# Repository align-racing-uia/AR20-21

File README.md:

<h1 align="center"> Align Racing 2021 </h1> <br>
<p align="center">
    
</p>

<!-- START doctoc generate TOC please keep comment here to allow auto update -->
<!-- DON'T EDIT THIS SECTION, INSTEAD RE-RUN doctoc TO UPDATE -->
## Table of contents

- [Introduction](#introduction)
- [Align Racing UiA](#alignracinguia)
- [Rules for file structure](#rulesforfilestructure)
- [License](#license)

<!-- END doctoc generated TOC please keep comment here to allow auto update -->

## Introduction

This is the repository for Align Racing's formula student race car's different systems.

## Align Racing UiA

<a href="http://www.alignracing.no/">Align Racing UiA (AR)</a> is a multidisciplinary student organisation at <a href="https://www.uia.no/">The University of Agder (UiA)</a>, that take part in the world’s largest yearly engineering competition; <a href="https://www.imeche.org/events/formula-student">Formula Student (FS)</a>. The organisation continuously consists of around 60 students, from a wide variety of disciplines. The competition includes developing, building, budgeting and marketing a small scale formula type racing car. AR takes this a bit further by having more focus on developing a strong organisation, open for all disciplines, that gives the members a taste of future work-life.

## Rules for directory structure
<h4>General directory structure:</h4>

* AR”YEAR”
    * AR”YEAR”_“PROJECT”
        - AR”YEAR”_“SUBPROJECT”
            - “PROJECT”_code
            - “PROJECT”_datasheets
            - “PROJECT”_images
            - “PROJECT”_schematic
            - “PROJECT”_simulink

<h4>Directory structure example:</h4>

* AR19
    * AR19_ETC
        - AR19_ETC_ACM_ETB
            - ACM_ETB_code
            - ACM_ETB_datasheets
            - ACM_ETB_images
            - ACM_ETB_schematic
            - ACM_ETB_simulink

## License
All content included in this Git repository is under the license:

Creative Commons Attribution-NonCommercial-ShareAlike 4.0 International

You are free to:
* <b> Share </b> — copy and redistribute the material in any medium or format
* <b> Adapt </b> — remix, transform, and build upon the material

Under the following terms:
* <b> Attribution </b> — You must give appropriate credit, provide a link to the license, and indicate if changes were made. You may do so in any reasonable manner, but not in any way that suggests the licensor endorses you or your use.
* <b> NonCommercial </b> — You may not use the material for commercial purposes.
* <b> ShareAlike </b> — If you remix, transform, or build upon the material, you must distribute your contributions under the same license as the original.
* <b> No additional restrictions </b> — You may not apply legal terms or technological measures that legally restrict others from doing anything the license permits.

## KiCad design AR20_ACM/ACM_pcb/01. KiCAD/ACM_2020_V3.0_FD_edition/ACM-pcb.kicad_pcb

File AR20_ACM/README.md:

## ACM 2020

### Changelog:

**27.07.2019:**
- Added: Protection circuit
- Added: Atmega Clock pass-through
- Moved: External oscillator from MCP to Atmega.

**28.07.2019:**
- Changed:	Orientation of tag connector in schematics
- Added:	Connector with I/O
- Added:	Overcurrent protection with polyfuse
- Added:	Overvoltage protection with zener diode
- Added:	Reverse polarity protection with diode
- Generated:Bill of Materials
- Added:	JAE IL-WX Series 0.8mm Pitch 30 Way connector
- Added:	RGB LED
- Added: P-mosfet for reverse polarity-protection
- Positioned power management (OC, OV, RP) in a 12x4mm space.
- Started tracing

**29.07.2019:**
- Moved: Protection circuit
- Changed board layout
- Changed viasize from 0.2 to 0.3
- Routing of tracks

**30.07.2019:**
- Added 3D components
- Removed all Tracks
- Added DC/DC converter
- Changed footprint of connector
- Added LP-filter to Atmega Avcc (Datasheet page 348)

**03.08.2019:**
- Changed folder structure
- Added mounting hole in schematics
- Removed LDO
- Added 5V switching regulator
- Changed Connector footprint
- Added track and via info from JLCPCB (2-Layers)

**04.08.2019:**
- Completed BOM on Google Drive
- Added 2x 10uF input Capacitor for regulator
- Moved documentation to main

**06.10.2019:**
- Moved resistors and capacitors away from microcontrollers
- Changed from Atmega328PB to Atmega328P (NB! Need to check circuit PWM and such)
- Disconnected all output pins on the Atmega328P
- Created a ACM simulation folder
- Connected pins that are equal to Atmega328PB

**26.09.2020:**
- Changed reverse polarity protection
- Added 5v USB backwards current protection

**27.09.2020** 
- Changed RGB led from from common Anode to common Cathode

**30.09.2020 - V3.0**
- Started upgrading to CAN FD chips. 

### ACM 2019 - Documentation

List of possible imporvements for ACM 2019
  + Remove the Fuse as it is 20\% of the total cost. Change it to a soldered SMD fuse or a diode.
   % Soruce https://docs.google.com/spreadsheets/d/1aR7CLCnCkN-1Qp3qICuXivDnihjTyPiA6Gjus2cEa0c/edit#gid=311613741&range=R12:R13
  
  + More I/O (Especially 2 interrupt) or change board dimension ratio. (1:1) like a flight controller
  
  + Remove castellated holes, since it makes the boards less reliable, and are also harder to manufacture.  
  
  + Change the led to a larger led for easy board manufacturing.
  
  + Change I/O to only one side of the board for hot swap.
  
  + ICSP take a large amout of space, change it to pads or small programming connector.
  
  + Change the width of the PCB to X*2,54mm so that it fits standard pin layout
  
  + Remove clock capacitors as "CSTNE16M0V530000R0" got 15uF embedded. Doesn't not require external load capacitors
  
  + Add a diode with a capacitor after. ACM reset due to low voltage when high current draw.
  
  + Possibility for UART out
  
  + Add low pass filter for the A/D converter (AVcc input) (See page 14 in 328p datasheet)

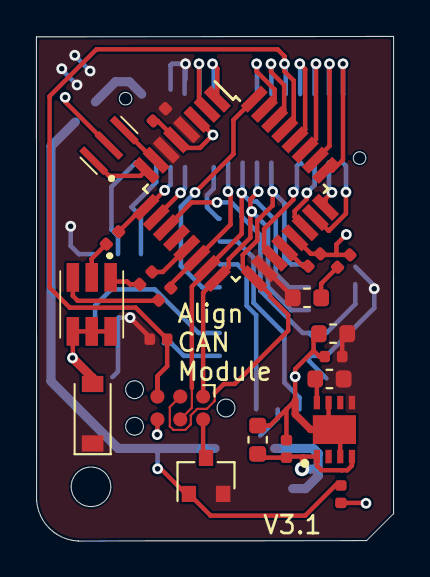
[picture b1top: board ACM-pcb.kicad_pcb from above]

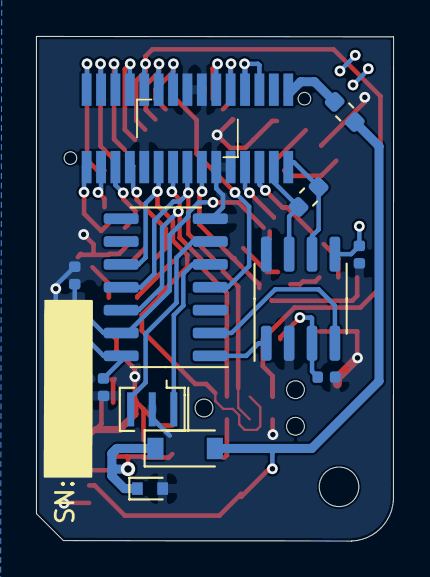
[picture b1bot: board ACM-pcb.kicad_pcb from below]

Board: 2 copper layers, 19.8 x 28.0 mm, 34 parts (13 on the bottom side), 42 nets.

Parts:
C1, C2, C3, C4, C5, C6, C7, C8: 0.1uF; C_0402_1005Metric
C10, C11: 10uF; C_0603_1608Metric
D1: 15V; D_SOD-523
D2: D_Zener_KDZVTR5.6B; D_Zener_KDZV5.6B_SOD-123
D4: D_Schottky_MBR0520LT1G; D_schotky_MBR0520LT1G
F1: 250mA; Fuse_0603_1608Metric
H1: M2 Mouting hole; MountingHole_2.2mm_M2
J1: TC2030-MCP-NL; Tag-Connect_TC2030-IDC-NL_2x03_P1.27mm_Vertical
L1: 10uH; L_0603_1608Metric
L2: 2.2 µH; L_0603_1608Metric
LED1: ASMB-TTF0-0A20B; ASMBTTF00A20B
P1: Conn_02x15_Odd_Even; IL-WX-30SB-VF-BE
Q1: Q_PMOS_DMP3099L-13; Pmos_DMP3099L-13
R1, R2, R6: 10K Ohm; R_0402_1005Metric
R3: 220Ω; R_0402_1005Metric
R4: 200Ω; R_0402_1005Metric
R5: 190Ω; R_0402_1005Metric
R7: 120Ω; R_0603_1608Metric
U1: ATmega328P-AU; TQFP-32_7x7mm_P0.8mm
U2: MCP2542FDxMF; SOIC_MCP2542FD
U3: NCV890430MW50TXG; SON65P300X300X100-9N
U4: MCP2517FD-xSL; Can_MCP2517FD_SOIC
Y1: 16.0Mhz; CSTNE16M0V530000R0
Y2: 20.0 Mhz; Resonator_CSTNE20M0V51Z000R0

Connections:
12V_fused: D4.2, F1.1, Q1.1, R2.2
+5V: C1.1, C5.1, C6.1, C7.1, C8.2, C11.1, D2.1, L1.1, L2.2, P1.24, P1.26, Q1.2, R1.1, R6.1, U1.4, U1.6, U1.18, U2.3, U2.5, U3.5, U4.14
+12V: F1.2, P1.30
+12V_Safe: C4.1, C10.1, D1.1, D4.1, U3.1, U3.4
/BLUE_LED: P1.17, R5.2, U1.14
/CAN_CS: R6.2, U1.11, U4.13
/CAN_INT: U1.32, U4.4
/GREEN_LED: P1.25, R4.2, U1.9
/MISO: J1.1, P1.13, U1.16, U4.12
/MOSI: J1.4, P1.15, U1.15, U4.11
/RED_LED: R3.2, U1.13
/RXCAN: U2.4, U4.2
/Reset: J1.5, P1.10, R1.2, U1.29
/SCK: J1.3, P1.11, U1.17, U4.10
/TXCAN: U2.1, U4.1
/U-Pin1: P1.1, U1.23
/U-Pin2: P1.2, U1.25
/U-Pin3: P1.3, U1.24
/U-Pin4: P1.4, U1.26
/U-Pin5: P1.5, U1.22
/U-Pin6: P1.6, U1.27
/U-Pin7: P1.7, U1.19
/U-Pin8: P1.8, U1.28
/U-Pin12: P1.12, U1.30
/U-Pin14: P1.14, U1.31
/U-Pin20: P1.20, U1.1
/U-Pin22: P1.22, U1.2
/U-Pin23: P1.23, U1.10
/U-Pin27: P1.27, R7.1, U2.7
/U-Pin29: P1.29, R7.2, U2.6
GND: C1.2, C2.2, C3.1, C4.2, C5.2, C6.2, C7.2, C8.1, C10.2, C11.2, D1.2, D2.2, J1.6, LED1.2, LED1.4, LED1.6, P1.9, P1.16, P1.18, P1.19, P1.21, R2.1, U1.3, U1.5, U1.21, U2.2, U2.8, U3.3, U3.7, U3.9, U4.7, Y1.2, Y2.2
unnamed: C2.1, U1.20
unnamed: C3.2, L1.2
unnamed: J1.2, Q1.3
unnamed: L2.1, U3.8
unnamed: LED1.1, R3.1
unnamed: LED1.3, R4.1
unnamed: LED1.5, R5.1
unnamed: U1.7, Y1.3
unnamed: U1.8, Y1.1
unnamed: U4.5, Y2.1
unnamed: U4.6, Y2.3

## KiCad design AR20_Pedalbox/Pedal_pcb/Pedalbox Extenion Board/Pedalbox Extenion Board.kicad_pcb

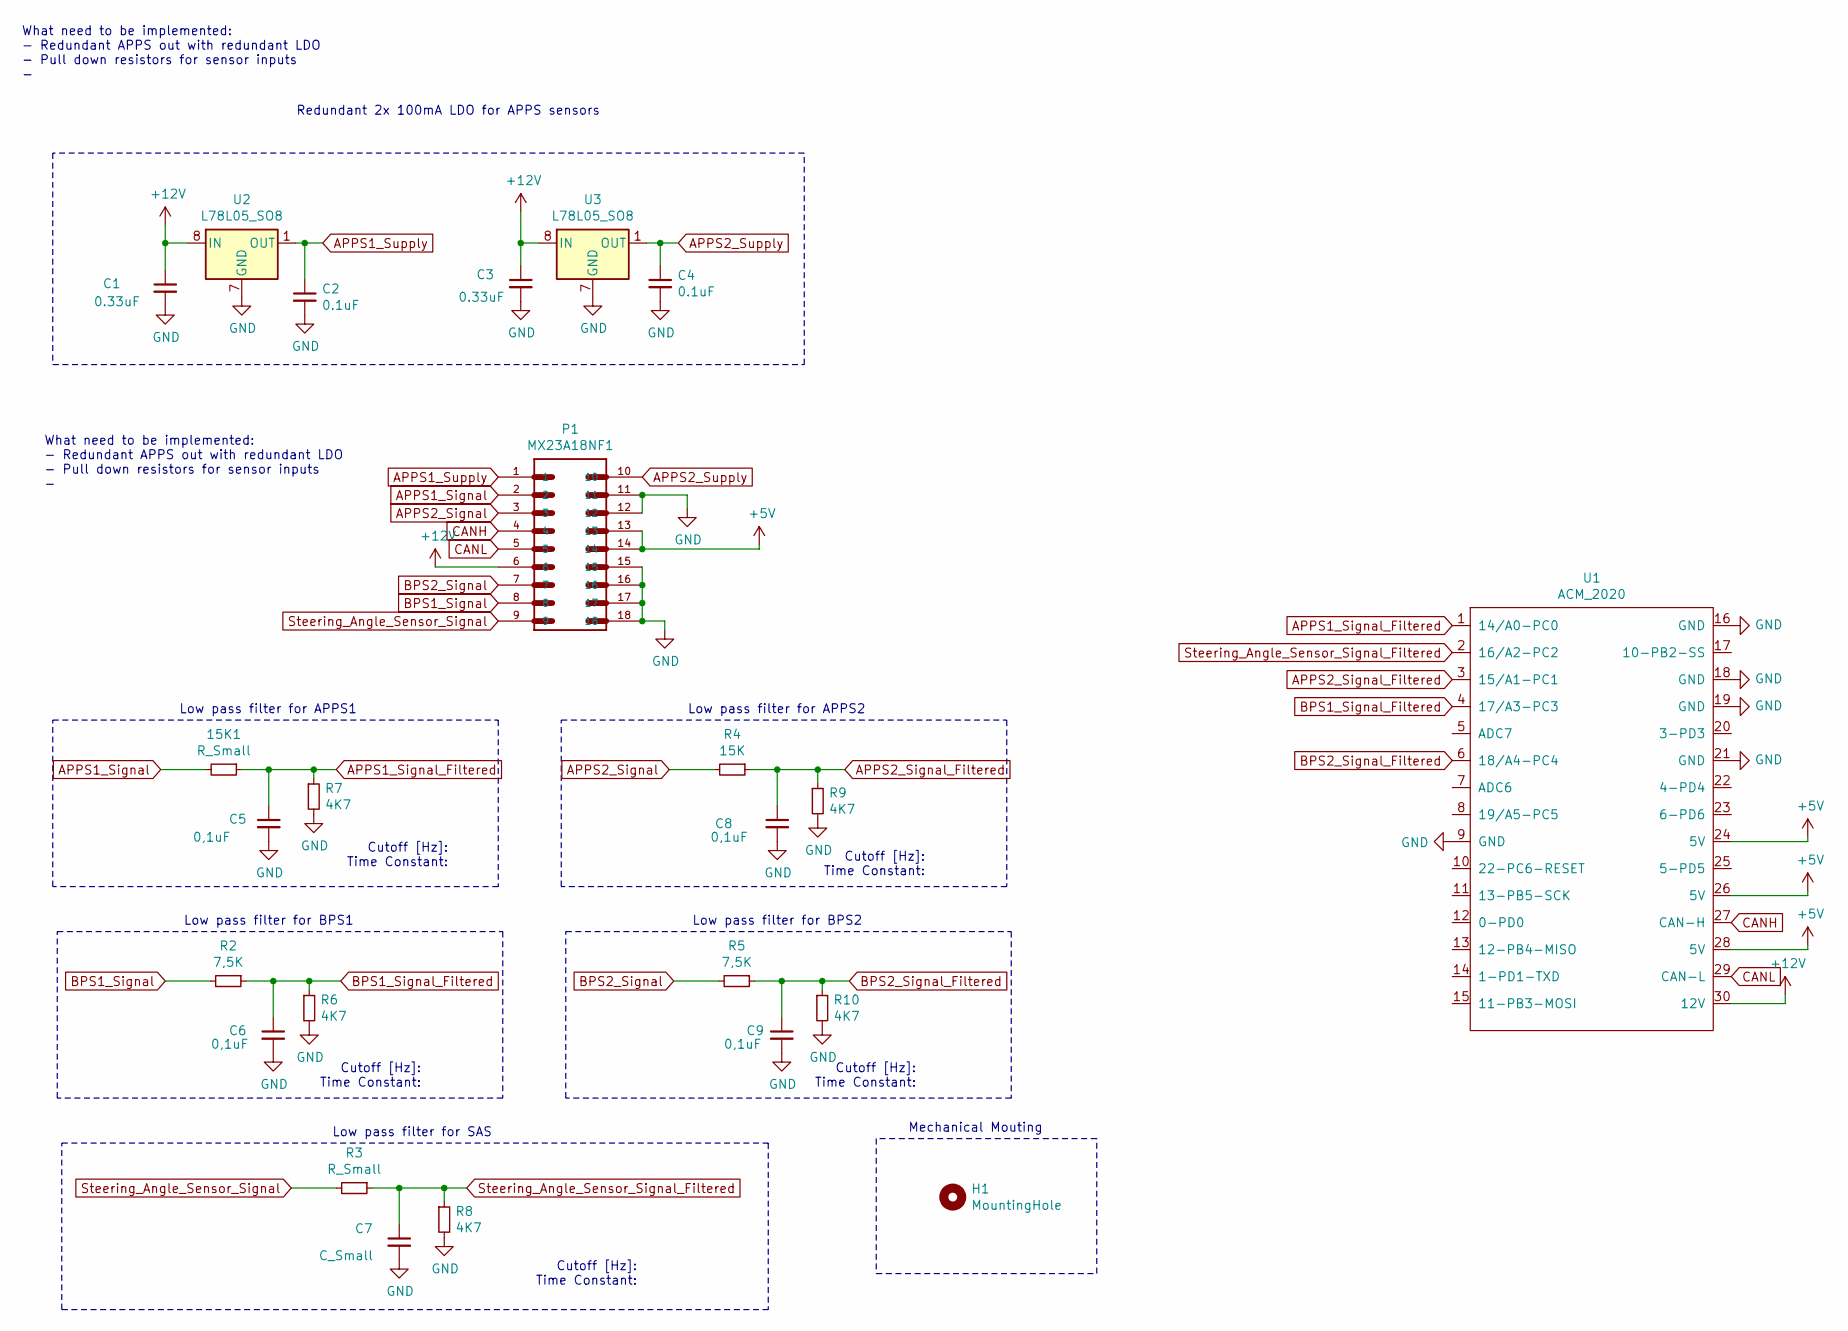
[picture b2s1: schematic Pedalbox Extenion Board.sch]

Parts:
15K1: R_Small; R_0603_1608Metric_Pad1.05x0.95mm_HandSolder
C1, C3: 0.33uF; C_0603_1608Metric_Pad1.05x0.95mm_HandSolder
C2, C4: 0.1uF; C_0603_1608Metric_Pad1.05x0.95mm_HandSolder
C5, C6, C8, C9: 0,1uF; C_0603_1608Metric_Pad1.05x0.95mm_HandSolder
C7: C_Small; C_0603_1608Metric_Pad1.05x0.95mm_HandSolder
H1: MountingHole; MountingHole_2.2mm_M2
P1: MX23A18NF1; JAE_MX23A18NF1
R2, R5: 7,5K; R_0603_1608Metric_Pad1.05x0.95mm_HandSolder
R3: R_Small; R_0603_1608Metric_Pad1.05x0.95mm_HandSolder
R4: 15K; R_0603_1608Metric_Pad1.05x0.95mm_HandSolder
R6, R7, R8, R9, R10: 4K7; R_0603_1608Metric_Pad1.05x0.95mm_HandSolder
U1: ACM_2020; ACM_2020_Footprint_wo_silk
U2, U3: L78L05_SO8; SOIC-8_3.9x4.9mm_P1.27mm

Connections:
+5V: P1.13, P1.14, U1.24 (5V), U1.26 (5V), U1.28 (5V)
+12V: C1.1, C3.1, P1.6, U1.30 (12V), U2.8 (IN), U3.8 (IN)
APPS1_Signal: 15K1.2, P1.2
APPS1_Signal_Filtered: 15K1.1, C5.1, R7.1, U1.1 (14/A0-PC0)
APPS1_Supply: C2.1, P1.1, U2.1 (OUT)
APPS2_Signal: P1.3, R4.2
APPS2_Signal_Filtered: C8.1, R4.1, R9.1, U1.3 (15/A1-PC1)
APPS2_Supply: C4.1, P1.10, U3.1 (OUT)
BPS1_Signal: P1.8, R2.2
BPS1_Signal_Filtered: C6.1, R2.1, R6.1, U1.4 (17/A3-PC3)
BPS2_Signal: P1.7, R5.2
BPS2_Signal_Filtered: C9.1, R5.1, R10.1, U1.6 (18/A4-PC4)
CANH: P1.4, U1.27 (CAN-H)
CANL: P1.5, U1.29 (CAN-L)
GND: C1.2, C2.2, C3.2, C4.2, C5.2, C6.2, C7.2, C8.2, C9.2, P1.11, P1.12, P1.15, P1.16, P1.17, P1.18, R6.2, R7.2, R8.2, R9.2, R10.2, U1.9 (GND), U1.16 (GND), U1.18 (GND), U1.19 (GND), U1.21 (GND), U2.2 (GND), U2.3 (GND), U2.6 (GND), U2.7 (GND), U3.2 (GND), U3.3 (GND), U3.6 (GND), U3.7 (GND)
Steering_Angle_Sensor_Signal: P1.9, R3.2
Steering_Angle_Sensor_Signal_Filtered: C7.1, R3.1, R8.1, U1.2 (16/A2-PC2)

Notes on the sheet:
Redundant 2x 100mA LDO for APPS sensors
What need to be implemented: - Redundant APPS out with redundant LDO - Pull down resistors for sensor inputs -
Low pass filter for APPS1
Low pass filter for APPS2
Cutoff [Hz]: Time Constant:
Low pass filter for BPS1
Low pass filter for BPS2
Low pass filter for SAS
Mechanical Mouting

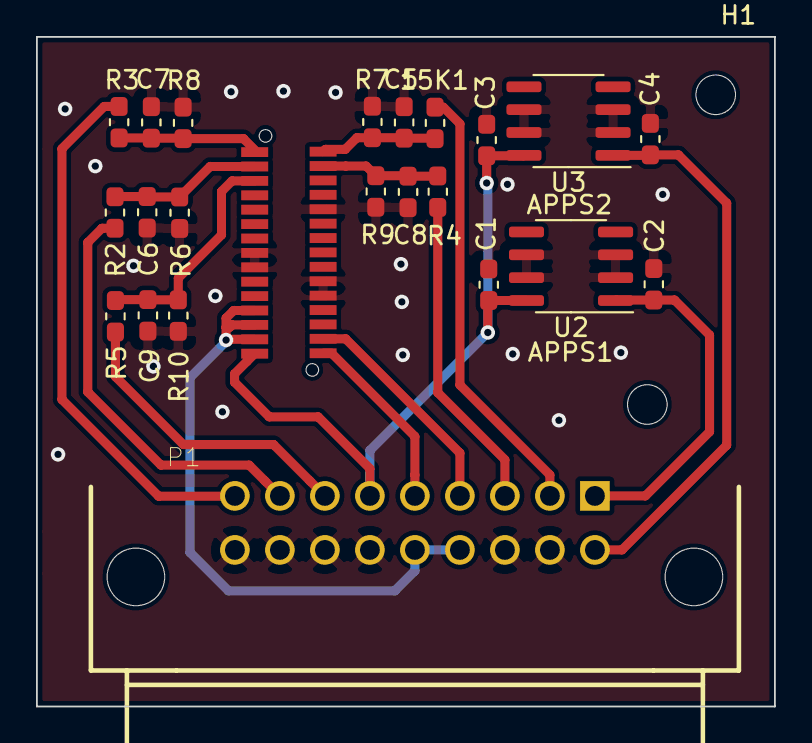
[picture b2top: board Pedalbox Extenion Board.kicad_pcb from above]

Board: 2 copper layers, 41.0 x 37.2 mm, 24 parts (0 on the bottom side), 17 nets.

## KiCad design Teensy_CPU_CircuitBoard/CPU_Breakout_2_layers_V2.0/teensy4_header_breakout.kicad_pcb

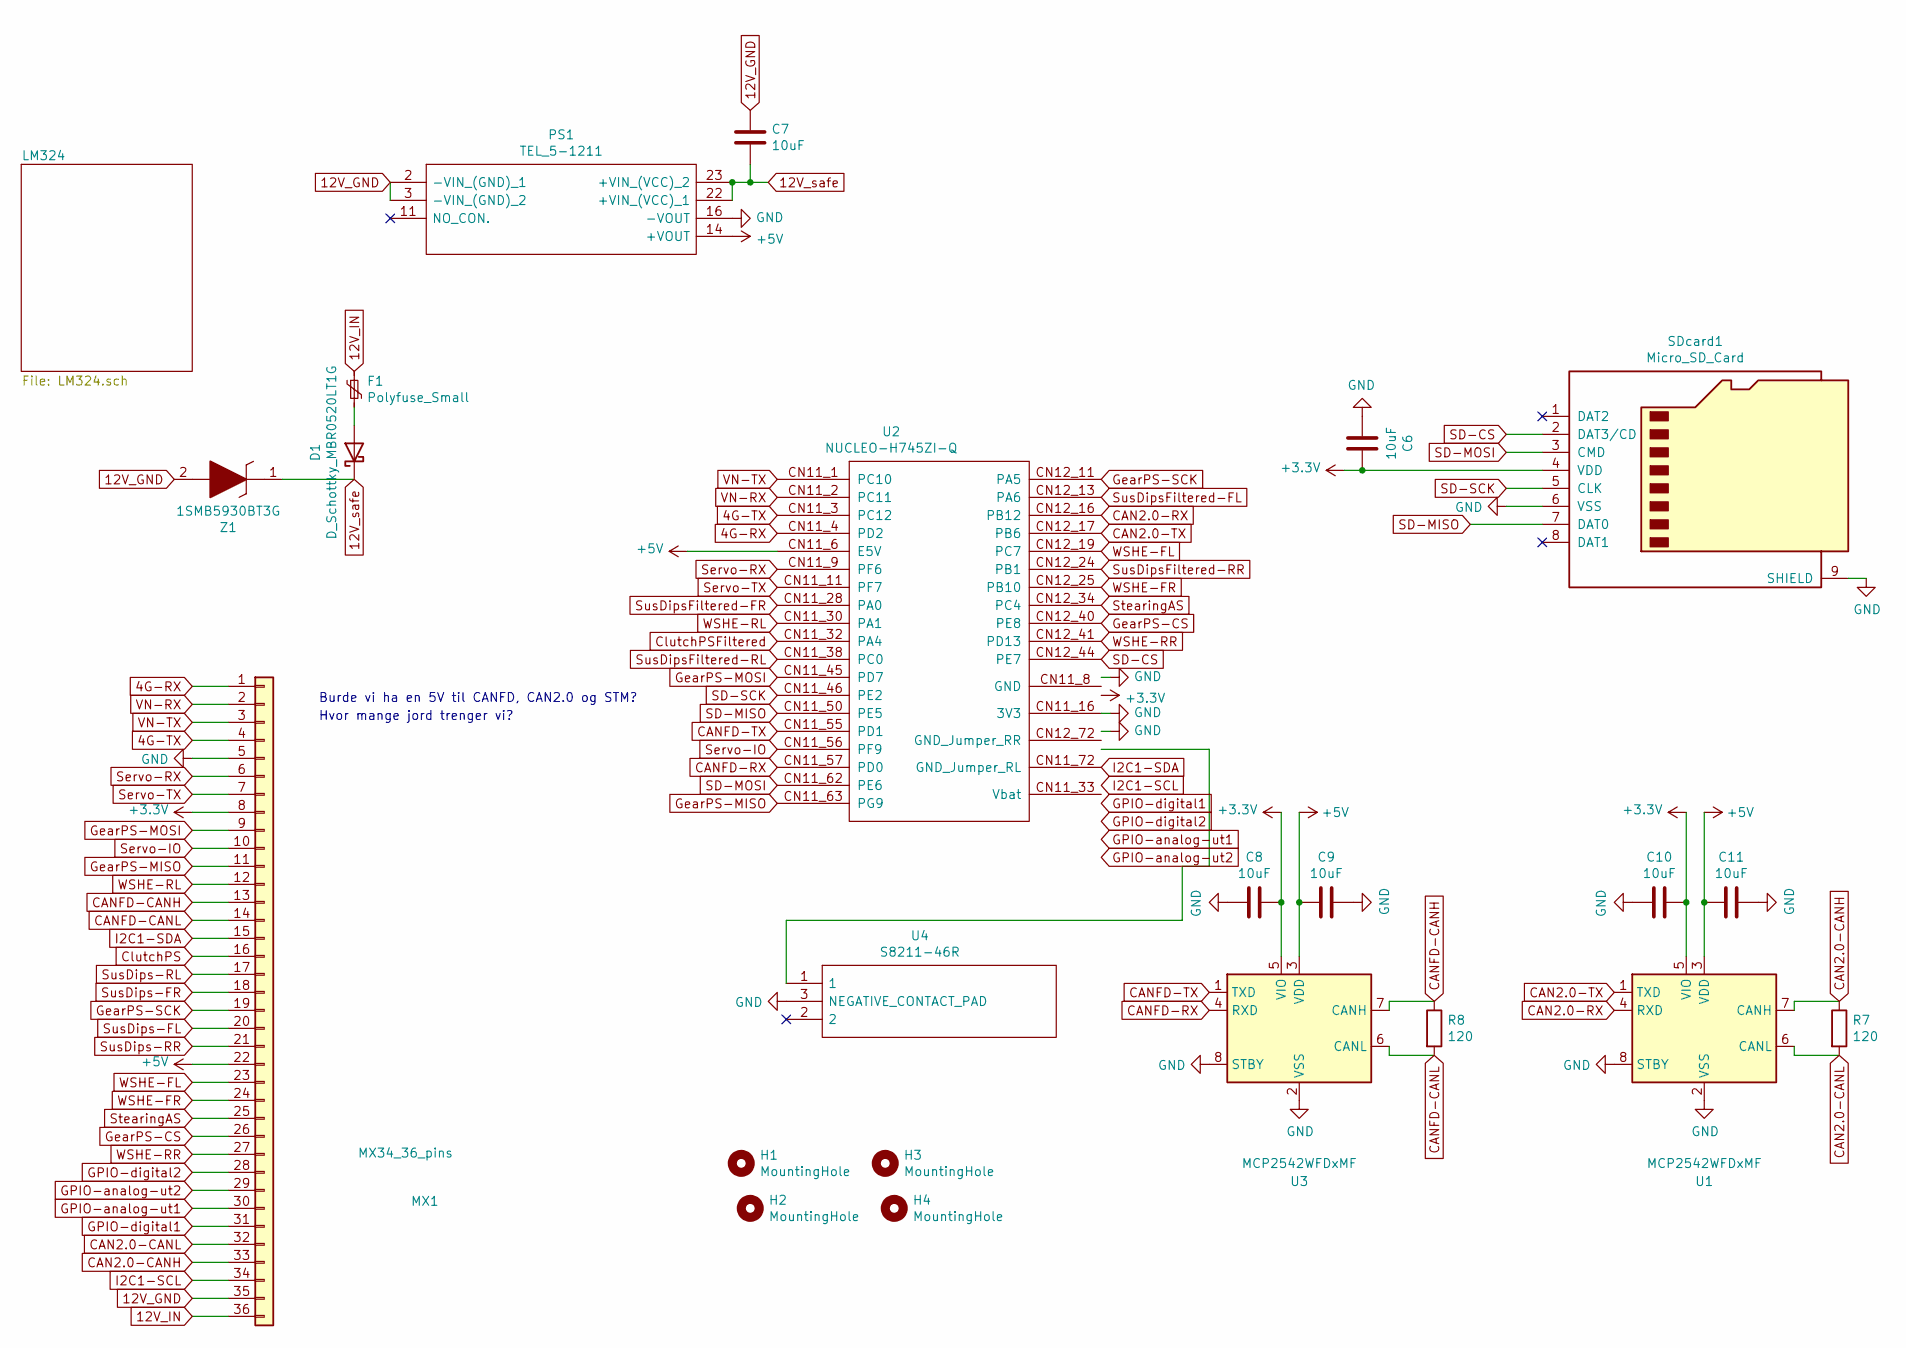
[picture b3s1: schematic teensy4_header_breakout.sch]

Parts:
C6, C7, C8, C9, C10, C11: 10uF; C_0603_1608Metric
D1: D_Schottky_MBR0520LT1G; D_SOD-123-MBR0520LT1G
F1: Polyfuse_Small; R_1210_3225Metric_Pad1.30x2.65mm_HandSolder
H1, H2, H3, H4: MountingHole; MountingHole_3.2mm_M3_ISO14580_Pad_TopBottom
MX1: MX34_36_pins; Connector_MX34_36pins
PS1: TEL_5-1211; TEL51211; Manufacturer_Part_Number TEL 5-1211; Mouser Part Number 495-TEL-5-1211
R7, R8: 120; R_0603_1608Metric_Pad0.98x0.95mm_HandSolder
SDcard1: Micro_SD_Card; Molex_502774-0891
U1, U3: MCP2542WFDxMF; DFN-8-1EP_3x3mm_P0.65mm_EP1.55x2.4mm
U2: NUCLEO-H745ZI-Q; MODULE_NUCLEO-F429ZI
U4: S8211-46R; Manufacturer_Part_Number S8211-46R; Mouser Part Number 855-S8211-46R
Z1: 1SMB5930BT3G; DIOM5436X247N; Manufacturer_Part_Number 1SMB5930BT3G; Mouser Part Number 863-1SMB5930BT3G

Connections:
4G-RX: MX1.1, U2.CN11_4 (PD2)
4G-TX: MX1.4, U2.CN11_3 (PC12)
12V_GND: C7.1, MX1.35, PS1.2 (-VIN_(GND)_1), PS1.3 (-VIN_(GND)_2), Z1.2
12V_IN: F1.1, MX1.36
12V_safe: C7.2, D1.1 (K), PS1.22 (+VIN_(VCC)_1), PS1.23 (+VIN_(VCC)_2), Z1.1
+5V: C9.1, C11.1, MX1.22, PS1.14 (+VOUT), U1.3 (VDD), U2.CN11_6 (E5V), U3.3 (VDD)
CAN2.0-CANH: MX1.33, R7.1, U1.7 (CANH)
CAN2.0-CANL: MX1.32, R7.2, U1.6 (CANL)
CAN2.0-RX: U1.4 (RXD), U2.CN12_16 (PB12)
CAN2.0-TX: U1.1 (TXD), U2.CN12_17 (PB6)
CANFD-CANH: MX1.13, R8.1, U3.7 (CANH)
CANFD-CANL: MX1.14, R8.2, U3.6 (CANL)
CANFD-RX: U2.CN11_57 (PD0), U3.4 (RXD)
CANFD-TX: U2.CN11_55 (PD1), U3.1 (TXD)
ClutchPS: MX1.16; also elsewhere on the board
ClutchPSFiltered: U2.CN11_32 (PA4); also elsewhere on the board
GPIO-analog-ut1: MX1.30, U2.CN12_50
GPIO-analog-ut2: MX1.29, U2.CN12_60
GPIO-digital1: MX1.31, U2.CN12_22
GPIO-digital2: MX1.28, U2.CN12_62
GearPS-CS: MX1.26, U2.CN12_40 (PE8)
GearPS-MISO: MX1.11, U2.CN11_63 (PG9)
GearPS-MOSI: MX1.9, U2.CN11_45 (PD7)
GearPS-SCK: MX1.19, U2.CN12_11 (PA5)
I2C1-SCL: MX1.34, U2.CN12_3
unnamed: D1.2 (A), F1.2
unnamed: U2.CN11_33 (Vbat), U4.1
SD-CS: SDcard1.2 (DAT3/CD), U2.CN12_44 (PE7)
SD-MISO: SDcard1.7 (DAT0), U2.CN11_50 (PE5)
SD-MOSI: SDcard1.3 (CMD), U2.CN11_62 (PE6)
SD-SCK: SDcard1.5 (CLK), U2.CN11_46 (PE2)
Servo-IO: MX1.10, U2.CN11_56 (PF9)
Servo-RX: MX1.6, U2.CN11_9 (PF6)
Servo-TX: MX1.7, U2.CN11_11 (PF7)
StearingAS: MX1.25, U2.CN12_34 (PC4)
SusDips-FL: MX1.20; also elsewhere on the board
SusDips-FR: MX1.18; also elsewhere on the board
SusDips-RL: MX1.17; also elsewhere on the board
SusDips-RR: MX1.21; also elsewhere on the board
SusDipsFiltered-FL: U2.CN12_13 (PA6); also elsewhere on the board
SusDipsFiltered-FR: U2.CN11_28 (PA0); also elsewhere on the board
SusDipsFiltered-RL: U2.CN11_38 (PC0); also elsewhere on the board
SusDipsFiltered-RR: U2.CN12_24 (PB1); also elsewhere on the board
VN-RX: MX1.2, U2.CN11_2 (PC11)
VN-TX: MX1.3, U2.CN11_1 (PC10)
WSHE-FL: MX1.23, U2.CN12_19 (PC7)
WSHE-FR: MX1.24, U2.CN12_25 (PB10)
WSHE-RL: MX1.12, U2.CN11_30 (PA1)
WSHE-RR: MX1.27, U2.CN12_41 (PD13)

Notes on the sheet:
Burde vi ha en 5V til CANFD, CAN2.0 og STM?
Hvor mange jord trenger vi?

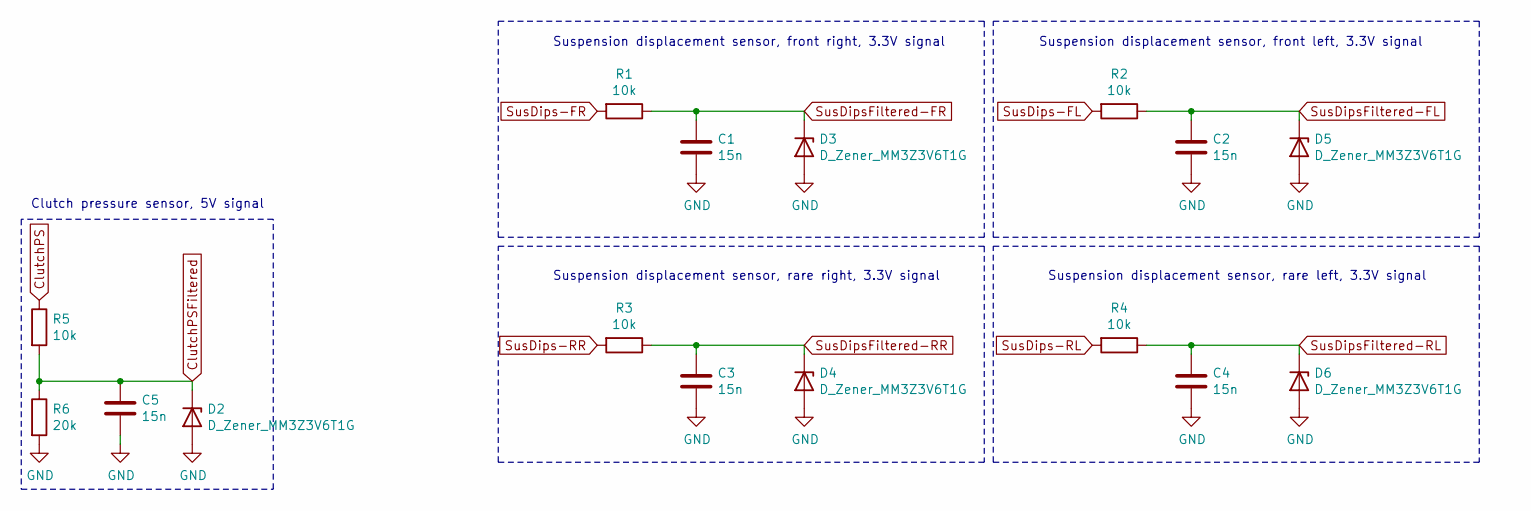
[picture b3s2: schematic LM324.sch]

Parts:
C1, C2, C3, C4, C5: 15n; C_0603_1608Metric
D2, D3, D4, D5, D6: D_Zener_MM3Z3V6T1G; D_0603_MM3Z3V6T1G
R1, R2, R3, R4, R5: 10k; R_0603_1608Metric
R6: 20k; R_0603_1608Metric

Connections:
ClutchPS: R5.1; also elsewhere on the board
ClutchPSFiltered: C5.1, D2.1 (K), R5.2, R6.1; also elsewhere on the board
SusDips-FL: R2.2; also elsewhere on the board
SusDips-FR: R1.2; also elsewhere on the board
SusDips-RL: R4.2; also elsewhere on the board
SusDips-RR: R3.2; also elsewhere on the board
SusDipsFiltered-FL: C2.1, D5.1 (K), R2.1; also elsewhere on the board
SusDipsFiltered-FR: C1.1, D3.1 (K), R1.1; also elsewhere on the board
SusDipsFiltered-RL: C4.1, D6.1 (K), R4.1; also elsewhere on the board
SusDipsFiltered-RR: C3.1, D4.1 (K), R3.1; also elsewhere on the board

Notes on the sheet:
Suspension displacement sensor, front right, 3.3V signal
Suspension displacement sensor, front left, 3.3V signal
Suspension displacement sensor, rare right, 3.3V signal
Suspension displacement sensor, rare left, 3.3V signal
Clutch pressure sensor, 5V signal

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
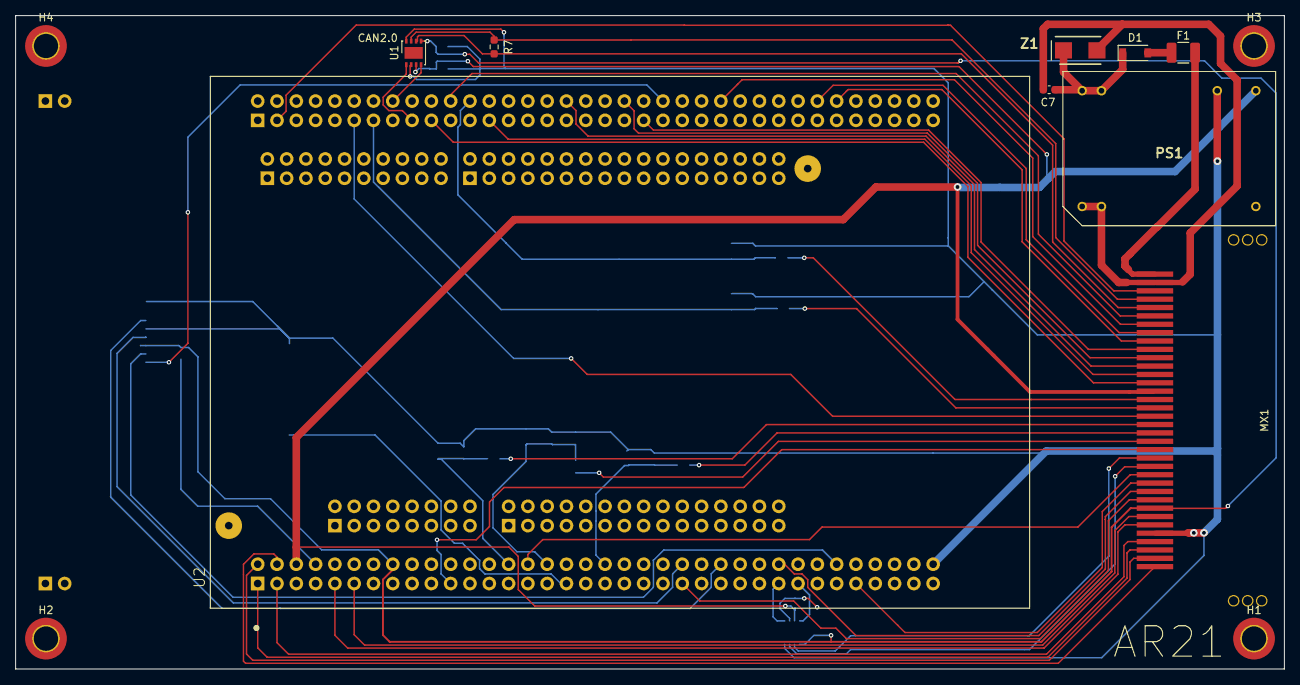
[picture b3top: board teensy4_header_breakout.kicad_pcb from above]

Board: 2 copper layers, 167.0 x 86.0 mm, 38 parts (0 on the bottom side), 52 nets.

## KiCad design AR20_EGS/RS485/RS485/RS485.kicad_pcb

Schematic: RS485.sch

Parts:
C1: 0.1uF; C_0402_1005Metric
D1: MM3Z3V6T1G; D_SOD-323
D2: MBR0520LT; D_SOD-123
J1: Conn_01x06_Female; PinSocket_1x06_P1.00mm_Vertical
J2: Conn_01x02_Female; PinSocket_1x02_P1.00mm_Vertical
Q1: PMOS_SQ2309ES-T1_GE3; PMOS_SQ2309ES
R1: R120Ω; C_0603_1608Metric
R2: R10kΩ; C_0603_1608Metric
U1: MAX3362EKA+T

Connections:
3.3_filtered: C1.2, D1.1, D2.1 (K), Q1.2, U1.8
*RX_Enable: J1.3, U1.2
+3V3: J1.1, Q1.3
/A: J2.1, R1.2, U1.6
/B: J2.2, R1.1, U1.7
GND: C1.1, D1.2, J1.6, R2.2, U1.5
unnamed: D2.2 (A), Q1.1, R2.1
RX: J1.2, U1.1
TX: J1.5, U1.4
TX_Enable: J1.4, U1.3

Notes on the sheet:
Reverse polarity protection

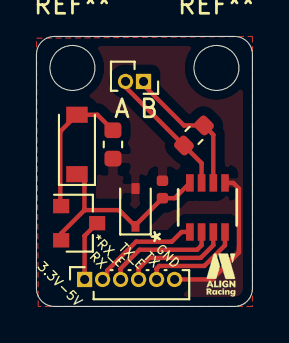
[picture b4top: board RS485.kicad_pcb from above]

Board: 2 copper layers, 12.0 x 15.0 mm, 9 parts (0 on the bottom side), 10 nets.

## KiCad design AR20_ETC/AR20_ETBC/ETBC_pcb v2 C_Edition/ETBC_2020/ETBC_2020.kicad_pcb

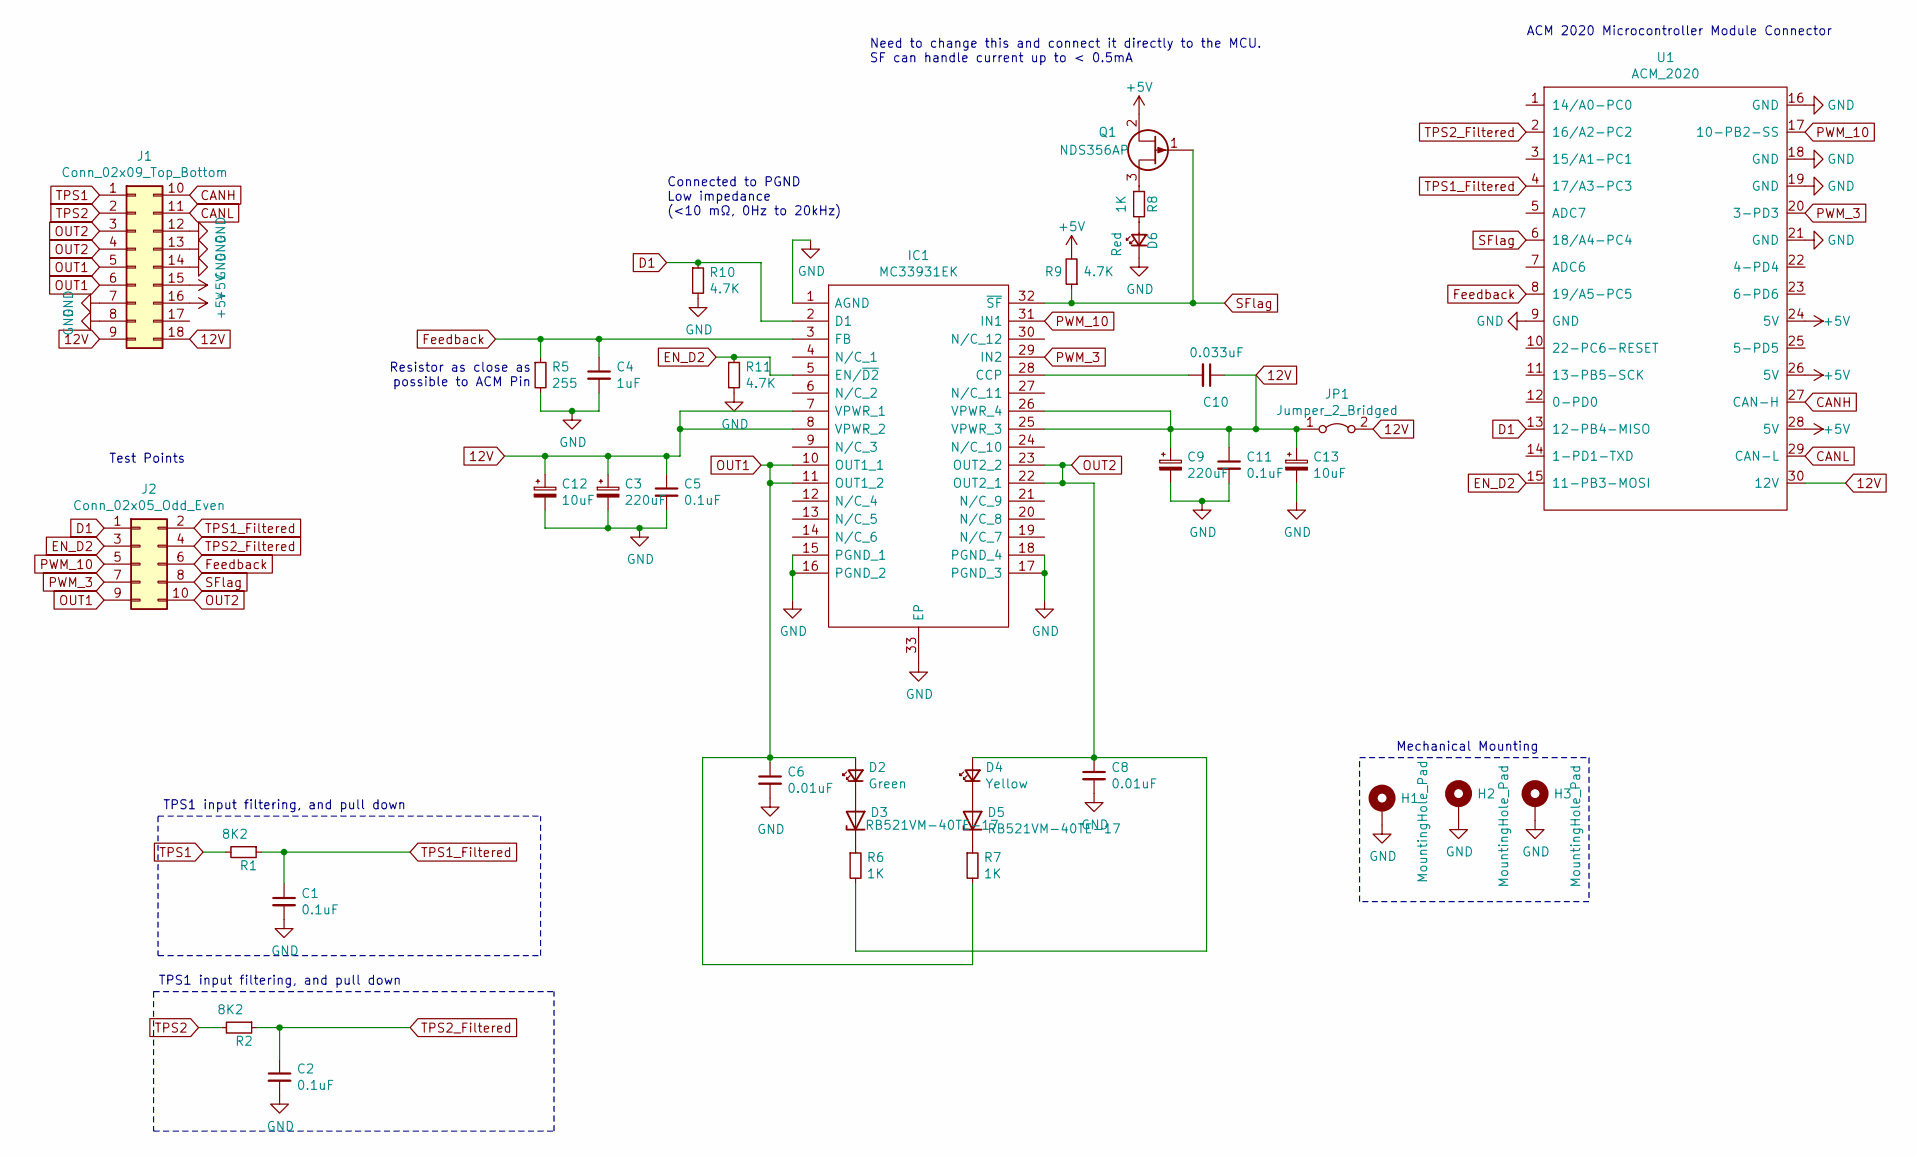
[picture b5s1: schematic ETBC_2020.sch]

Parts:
C1, C2, C5, C11: 0.1uF; C_0603_1608Metric_Pad1.05x0.95mm_HandSolder
C3, C9: 220uF; CP_Elec_6.3x7.7
C4: 1uF; C_0603_1608Metric_Pad1.05x0.95mm_HandSolder
C6, C8: 0.01uF; C_0603_1608Metric_Pad1.05x0.95mm_HandSolder
C10: 0.033uF; C_0603_1608Metric_Pad1.05x0.95mm_HandSolder
C12, C13: 10uF; CP_EIA-3216-10_Kemet-I_Pad1.58x1.35mm_HandSolder
D2: Green; D_1206_3216Metric_Pad1.42x1.75mm_HandSolder
D3, D5: RB521VM-40TE-17; D_SOD-323F
D4: Yellow; D_1206_3216Metric_Pad1.42x1.75mm_HandSolder
D6: Red; D_1206_3216Metric_Pad1.42x1.75mm_HandSolder
H1, H2, H3: MountingHole_Pad; MountingHole_3.2mm_M3_Pad_Via
IC1: MC33931EK; SOP65P1030X245-33N; Manufacturer_Part_Number MC33931EK; Mouser Part Number 841-MC33931EK
J1: Conn_02x09_Top_Bottom; JAE_MX23A18NF1
J2: Conn_02x05_Odd_Even; PinHeader_2x05_P2.54mm_Vertical
JP1: Jumper_2_Bridged; Jumper PWR 25 26
Q1: NDS356AP; SOT-23
R1, R2: 8K2; R_0603_1608Metric_Pad1.05x0.95mm_HandSolder
R5: 255; R_0603_1608Metric_Pad1.05x0.95mm_HandSolder
R6, R7, R8: 1K; R_0603_1608Metric_Pad1.05x0.95mm_HandSolder
R9, R10, R11: 4.7K; R_0603_1608Metric_Pad1.05x0.95mm_HandSolder
U1: ACM_2020; ACM_2020_Footprint_wo_silk

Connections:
12V: C3.1, C5.1, C9.1, C10.1, C11.1, C12.1, C13.1, IC1.7 (VPWR_1), IC1.8 (VPWR_2), IC1.25 (VPWR_3), IC1.26 (VPWR_4), J1.9, J1.18, JP1.1 (A), JP1.2 (B), U1.30 (12V)
+5V: J1.15, J1.16, Q1.2 (S), R9.2, U1.24 (5V), U1.26 (5V), U1.28 (5V)
CANH: J1.10, U1.27 (CAN-H)
CANL: J1.11, U1.29 (CAN-L)
D1: IC1.2 (D1), J2.1, R10.1, U1.13 (12-PB4-MISO)
EN_D2: IC1.5 (EN/~D2), J2.3, R11.1, U1.15 (11-PB3-MOSI)
Feedback: C4.1, IC1.3 (FB), J2.6, R5.1, U1.8 (19/A5-PC5)
GND: C1.2, C2.2, C3.2, C4.2, C5.2, C6.2, C8.2, C9.2, C11.2, C12.2, C13.2, D6.1 (K), H1.1, H2.1, H3.1, IC1.1 (AGND), IC1.15 (PGND_1), IC1.16 (PGND_2), IC1.17 (PGND_3), IC1.18 (PGND_4), IC1.33 (EP), J1.7, J1.8, J1.12, J1.13, J1.14, R5.2, R10.2, R11.2, U1.9 (GND), U1.16 (GND), U1.18 (GND), U1.19 (GND), U1.21 (GND)
unnamed: C10.2, IC1.28 (CCP)
unnamed: D2.1 (K), D3.2 (A)
unnamed: D3.1 (K), R6.1
unnamed: D4.1 (K), D5.2 (A)
unnamed: D5.1 (K), R7.1
unnamed: D6.2 (A), R8.2
unnamed: Q1.3 (D), R8.1
OUT1: C6.1, D2.2 (A), IC1.10 (OUT1_1), IC1.11 (OUT1_2), J1.5, J1.6, J2.9, R7.2
OUT2: C8.1, D4.2 (A), IC1.22 (OUT2_1), IC1.23 (OUT2_2), J1.3, J1.4, J2.10, R6.2
PWM_3: IC1.29 (IN2), J2.7, U1.20 (3-PD3)
PWM_10: IC1.31 (IN1), J2.5, U1.17 (10-PB2-SS)
SFlag: IC1.32 (~SF), J2.8, Q1.1 (G), R9.1, U1.6 (18/A4-PC4)
TPS1: J1.1, R1.2
TPS1_Filtered: C1.1, J2.2, R1.1, U1.4 (17/A3-PC3)
TPS2: J1.2, R2.2
TPS2_Filtered: C2.1, J2.4, R2.1, U1.2 (16/A2-PC2)

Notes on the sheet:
TPS1 input filtering, and pull down
Resistor as close as possible to ACM Pin
Connected to PGND Low impedance (<10 mΩ, 0Hz to 20kHz)
Need to change this and connect it directly to the MCU. SF can handle current up to < 0.5mA
Mechanical Mounting
Test Points
ACM 2020 Microcontroller Module Connector

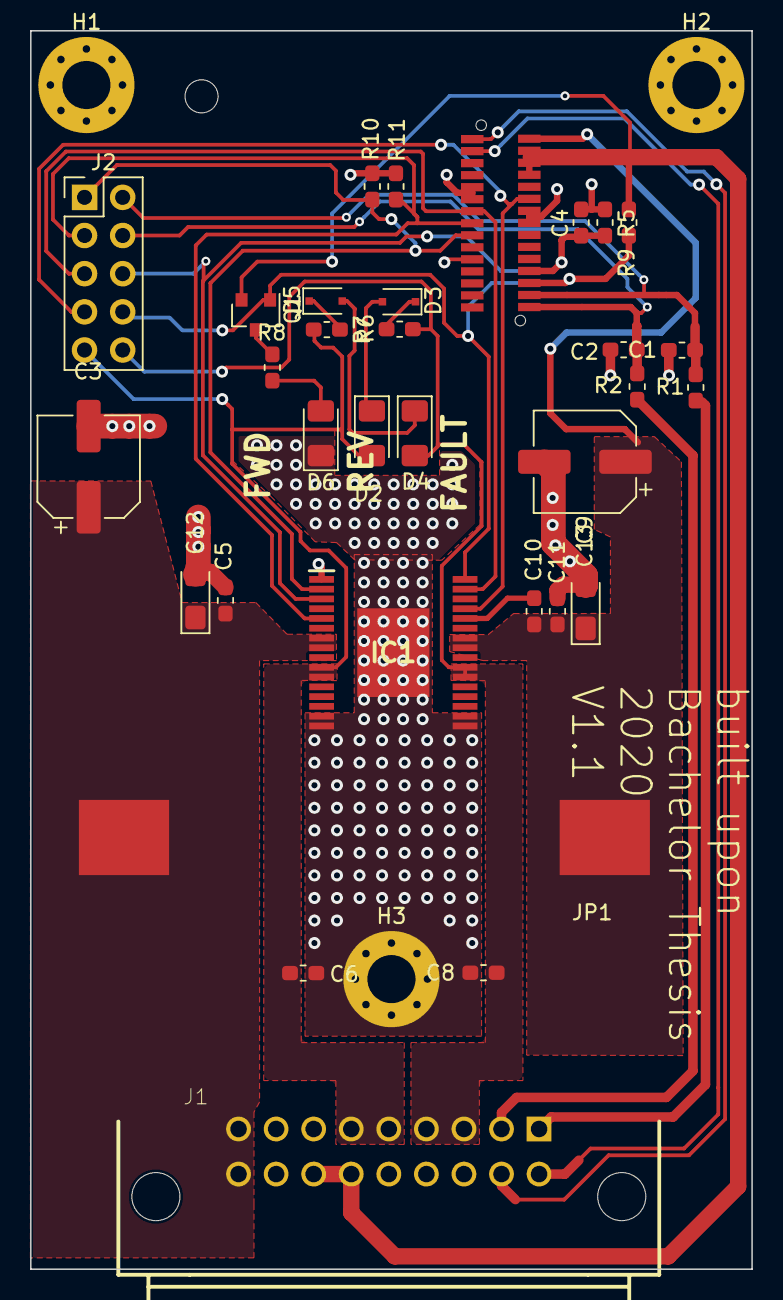
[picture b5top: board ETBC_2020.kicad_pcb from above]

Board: 2 copper layers, 48.0 x 82.4 mm, 35 parts (0 on the bottom side), 24 nets.

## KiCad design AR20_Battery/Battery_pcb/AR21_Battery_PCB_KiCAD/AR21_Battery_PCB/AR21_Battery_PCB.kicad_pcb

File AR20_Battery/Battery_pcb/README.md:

This is the PCB folder in battery.

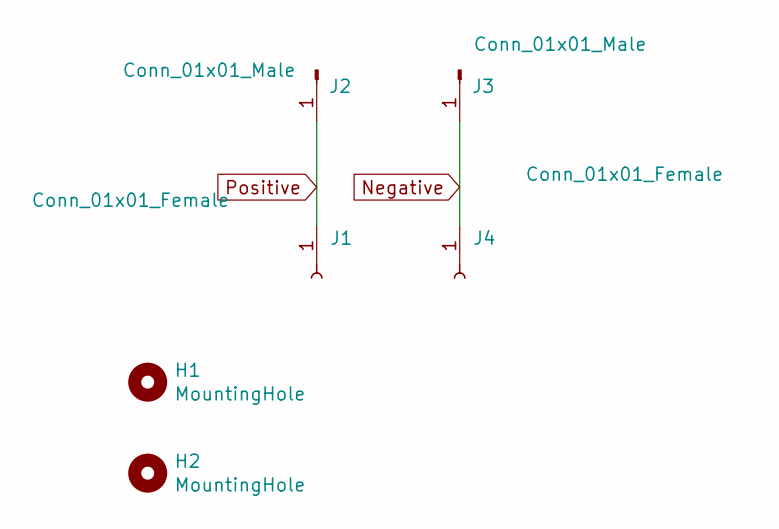
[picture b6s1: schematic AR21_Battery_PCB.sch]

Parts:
H1, H2: MountingHole; M3 hole
J1, J4: Conn_01x01_Female; Wurth_74655095R_Screw_Post
J2, J3: Conn_01x01_Male; Flat

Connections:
Negative: J3.1, J4.1
Positive: J1.1, J2.1

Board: 2 copper layers, 6 parts (2 on the bottom side), 2 nets, no tracks yet.

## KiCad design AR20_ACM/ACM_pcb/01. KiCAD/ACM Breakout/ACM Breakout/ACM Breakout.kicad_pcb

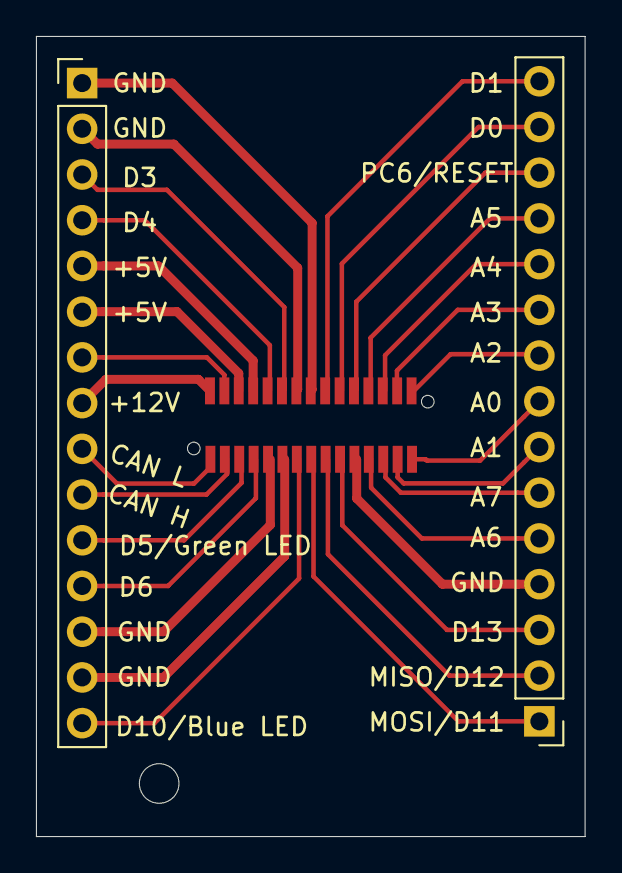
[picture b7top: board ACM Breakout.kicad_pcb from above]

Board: 2 copper layers, 30.5 x 44.5 mm, 3 parts (0 on the bottom side), 30 nets.

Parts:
J1, J2: Conn_01x15_Male; PinHeader_1x15_P2.54mm_Vertical
U1: ACM_2020; ACM_2020_Footprint_wo_silk

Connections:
/Pin1: J2.8, U1.1
/Pin2: J2.9, U1.2
/Pin3: J2.7, U1.3
/Pin4: J2.10, U1.4
/Pin5: J2.6, U1.5
/Pin6: J2.11, U1.6
/Pin7: J2.5, U1.7
/Pin8: J2.12, U1.8
/Pin9: J2.4, U1.9
/Pin10: J2.13, U1.10
/Pin11: J2.3, U1.11
/Pin12: J2.14, U1.12
/Pin13: J2.2, U1.13
/Pin14: J2.15, U1.14
/Pin15: J2.1, U1.15
/Pin16: J1.1, U1.16
/Pin17: J1.15, U1.17
/Pin18: J1.2, U1.18
/Pin19: J1.14, U1.19
/Pin20: J1.3, U1.20
/Pin21: J1.13, U1.21
/Pin22: J1.4, U1.22
/Pin23: J1.12, U1.23
/Pin24: J1.5, U1.24
/Pin25: J1.11, U1.25
/Pin26: J1.6, U1.26
/Pin27: J1.10, U1.27
/Pin28: J1.7, U1.28
/Pin29: J1.9, U1.29
/Pin30: J1.8, U1.30

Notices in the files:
parts and their libraries:
Copyright 2016 Accelerated Designs. All rights reserved.
